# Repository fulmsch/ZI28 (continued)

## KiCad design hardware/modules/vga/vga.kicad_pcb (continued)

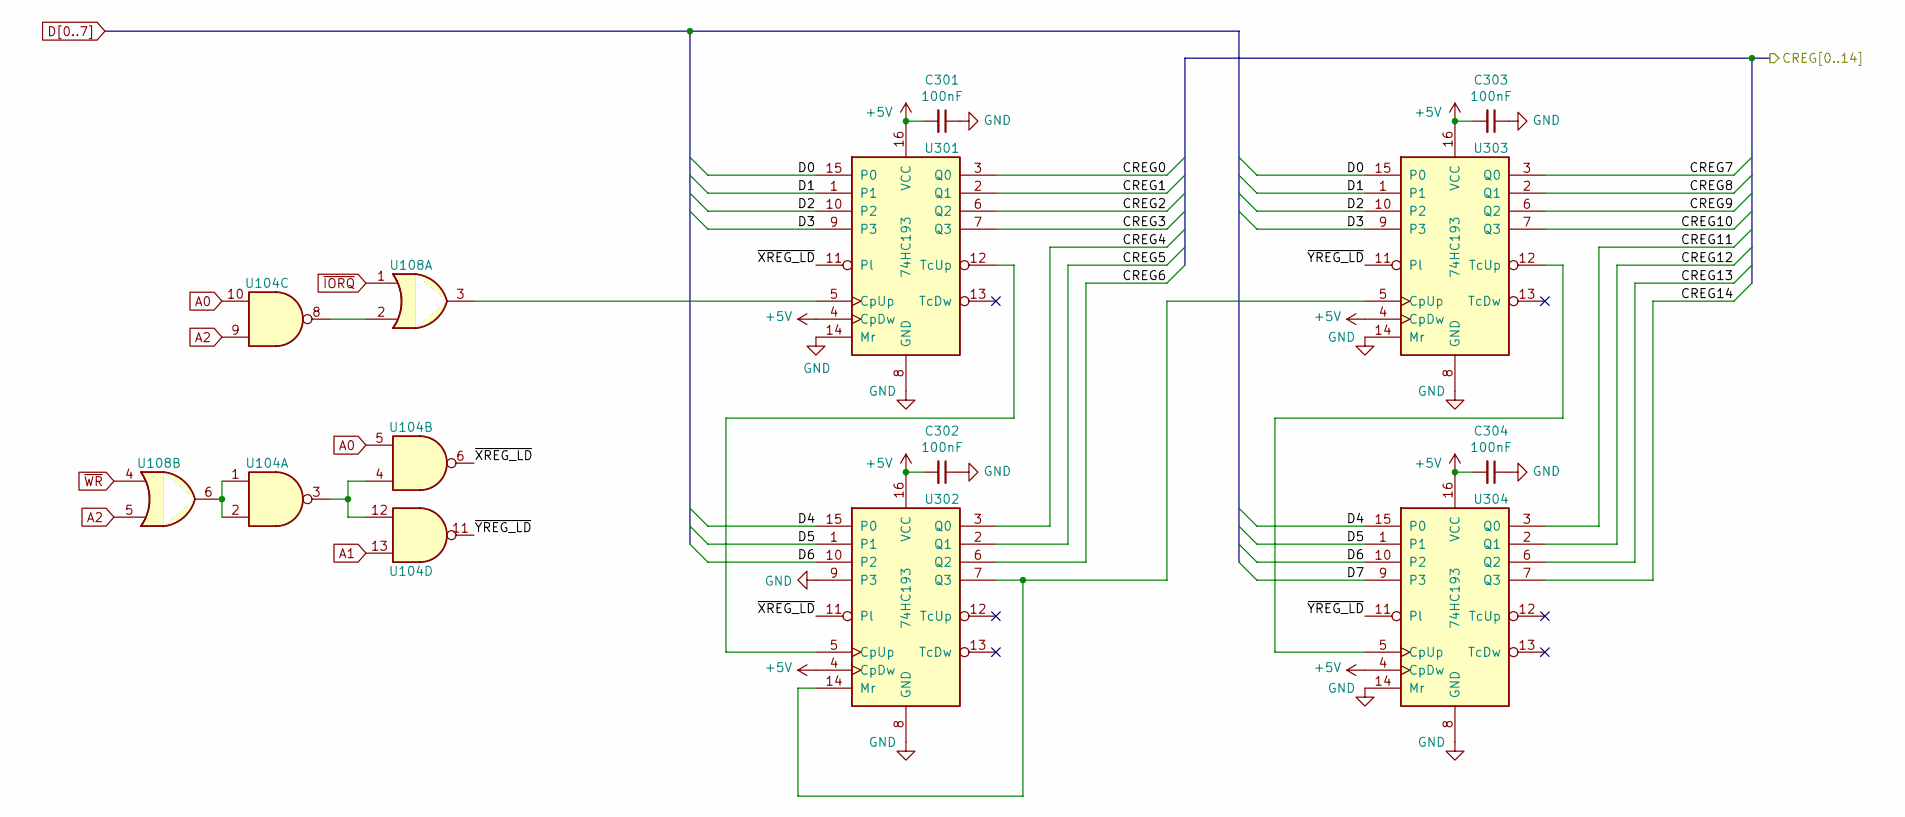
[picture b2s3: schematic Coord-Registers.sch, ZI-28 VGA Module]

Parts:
C301, C302, C303, C304: 100nF; C_Disc_D3.0mm_W1.6mm_P2.50mm
U104: 74HC00; DIP-14_W7.62mm_Socket
U108: 74HC32; DIP-14_W7.62mm_Socket
U301, U302, U303, U304: 74HC193; DIP-16_W7.62mm_Socket

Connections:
+5V: C301.2, C302.2, C303.2, C304.2, U301.4 (CpDw), U301.16 (VCC), U302.4 (CpDw), U302.16 (VCC), U303.4 (CpDw), U303.16 (VCC), U304.4 (CpDw), U304.16 (VCC); also elsewhere on the board
/Coordinate Registers/CREG0: U301.3 (Q0); also elsewhere on the board
/Coordinate Registers/CREG1: U301.2 (Q1); also elsewhere on the board
/Coordinate Registers/CREG2: U301.6 (Q2); also elsewhere on the board
/Coordinate Registers/CREG3: U301.7 (Q3); also elsewhere on the board
/Coordinate Registers/CREG4: U302.3 (Q0); also elsewhere on the board
/Coordinate Registers/CREG5: U302.2 (Q1); also elsewhere on the board
/Coordinate Registers/CREG6: U302.6 (Q2); also elsewhere on the board
/Coordinate Registers/CREG7: U303.3 (Q0); also elsewhere on the board
/Coordinate Registers/CREG8: U303.2 (Q1); also elsewhere on the board
/Coordinate Registers/CREG9: U303.6 (Q2); also elsewhere on the board
/Coordinate Registers/CREG10: U303.7 (Q3); also elsewhere on the board
/Coordinate Registers/CREG11: U304.3 (Q0); also elsewhere on the board
/Coordinate Registers/CREG12: U304.2 (Q1); also elsewhere on the board
/Coordinate Registers/CREG13: U304.6 (Q2); also elsewhere on the board
/Coordinate Registers/CREG14: U304.7 (Q3); also elsewhere on the board
/Coordinate Registers/~XREG_LD: U104.6, U301.11 (Pl), U302.11 (Pl)
/Coordinate Registers/~YREG_LD: U104.11, U303.11 (Pl), U304.11 (Pl)
A0: U104.5, U104.10; also elsewhere on the board
A1: U104.13; also elsewhere on the board
A2: U104.9, U108.5; also elsewhere on the board
D0: U301.15 (P0), U303.15 (P0); also elsewhere on the board
D1: U301.1, U303.1; also elsewhere on the board
D2: U301.10 (P2), U303.10 (P2); also elsewhere on the board
D3: U301.9 (P3), U303.9 (P3); also elsewhere on the board
D4: U302.15 (P0), U304.15 (P0); also elsewhere on the board
D5: U302.1, U304.1; also elsewhere on the board
D6: U302.10 (P2), U304.10 (P2); also elsewhere on the board
D7: U304.9 (P3); also elsewhere on the board
GND: C301.1, C302.1, C303.1, C304.1, U301.8 (GND), U301.14 (Mr), U302.8 (GND), U302.9 (P3), U303.8 (GND), U303.14 (Mr), U304.8 (GND), U304.14 (Mr); also elsewhere on the board
unnamed: U104.1, U104.2, U108.6
unnamed: U104.8, U108.2
unnamed: U104.3, U104.4, U104.12
unnamed: U108.3, U301.5 (CpUp)
unnamed: U301.12 (TcUp), U302.5 (CpUp)
unnamed: U302.7 (Q3), U302.14 (Mr), U303.5 (CpUp)
unnamed: U303.12 (TcUp), U304.5 (CpUp)
~IORQ: U108.1; also elsewhere on the board
~WR: U108.4; also elsewhere on the board

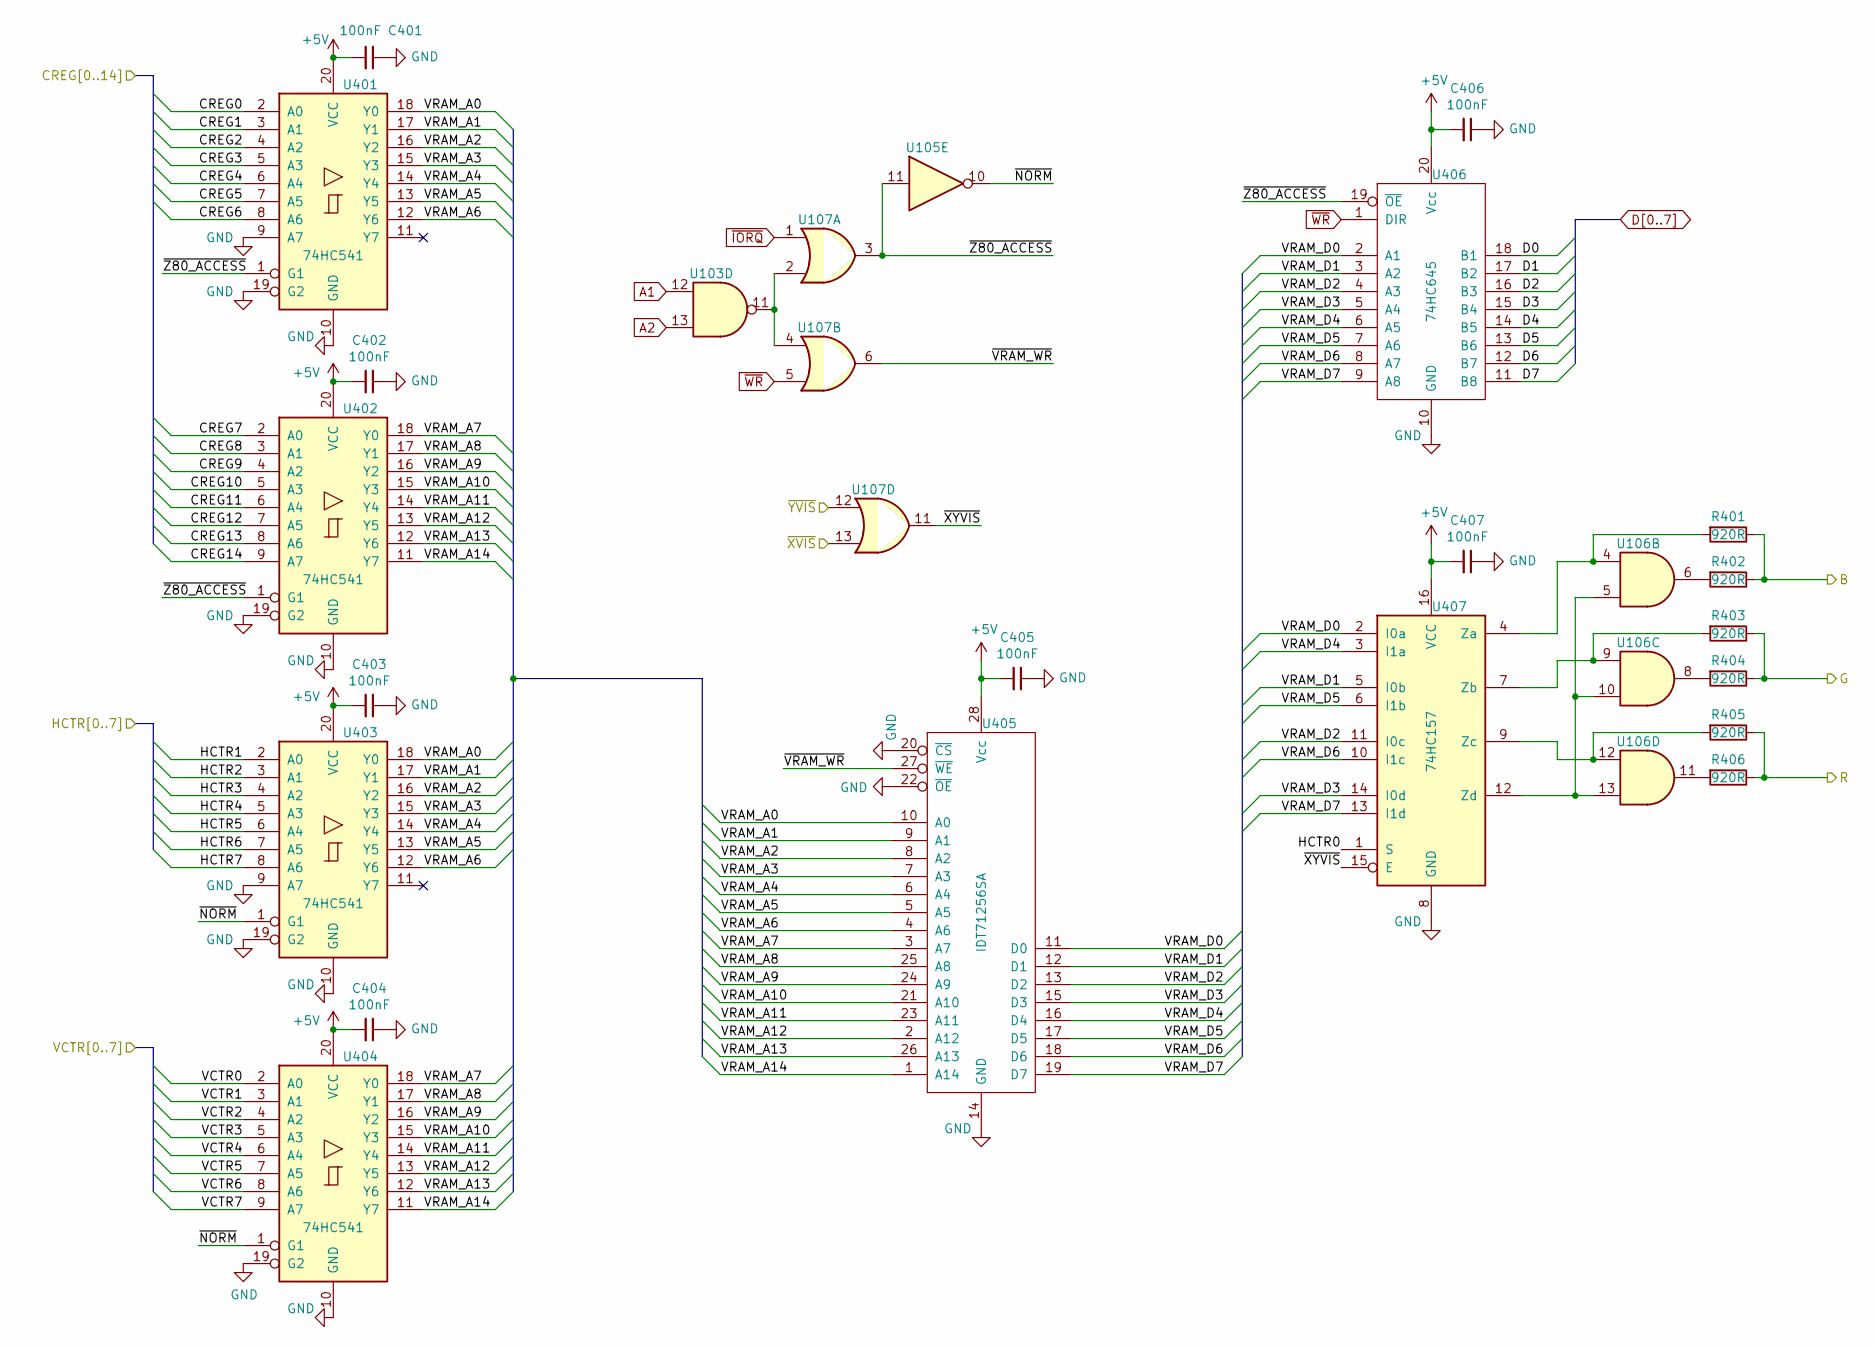
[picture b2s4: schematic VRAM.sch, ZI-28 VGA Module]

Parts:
C401, C402, C403, C404, C405, C406, C407: 100nF; C_Disc_D3.0mm_W1.6mm_P2.50mm
R401, R402, R403, R404, R405, R406: 920R; R_Axial_DIN0207_L6.3mm_D2.5mm_P2.54mm_Vertical
U103: 74HC00; DIP-14_W7.62mm_Socket
U105: 74HC04; DIP-14_W7.62mm_Socket
U106: 74HC08; DIP-14_W7.62mm_Socket
U107: 74HC32; DIP-14_W7.62mm_Socket
U401, U402, U403, U404: 74HC541; DIP-20_W7.62mm_Socket
U405: IDT71256SA; DIP-28_W7.62mm_Socket
U406: 74HC645; DIP-20_W7.62mm_Socket
U407: 74HC157; DIP-16_W7.62mm_Socket

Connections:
+5V: C401.2, C402.2, C403.2, C404.2, C405.2, C406.2, C407.2, U401.20 (VCC), U402.20 (VCC), U403.20 (VCC), U404.20 (VCC), U405.28 (Vcc), U406.20 (Vcc), U407.16 (VCC); also elsewhere on the board
/BLUE: R401.1, R402.1; also elsewhere on the board
/Coordinate Registers/CREG0: U401.2 (A0); also elsewhere on the board
/Coordinate Registers/CREG1: U401.3 (A1); also elsewhere on the board
/Coordinate Registers/CREG2: U401.4 (A2); also elsewhere on the board
/Coordinate Registers/CREG3: U401.5 (A3); also elsewhere on the board
/Coordinate Registers/CREG4: U401.6 (A4); also elsewhere on the board
/Coordinate Registers/CREG5: U401.7 (A5); also elsewhere on the board
/Coordinate Registers/CREG6: U401.8 (A6); also elsewhere on the board
/Coordinate Registers/CREG7: U402.2 (A0); also elsewhere on the board
/Coordinate Registers/CREG8: U402.3 (A1); also elsewhere on the board
/Coordinate Registers/CREG9: U402.4 (A2); also elsewhere on the board
/Coordinate Registers/CREG10: U402.5 (A3); also elsewhere on the board
/Coordinate Registers/CREG11: U402.6 (A4); also elsewhere on the board
/Coordinate Registers/CREG12: U402.7 (A5); also elsewhere on the board
/Coordinate Registers/CREG13: U402.8 (A6); also elsewhere on the board
/Coordinate Registers/CREG14: U402.9 (A7); also elsewhere on the board
/GREEN: R403.1, R404.1; also elsewhere on the board
/Pixel Counters/HCTR0: U407.1 (S); also elsewhere on the board
/Pixel Counters/HCTR1: U403.2 (A0); also elsewhere on the board
/Pixel Counters/HCTR2: U403.3 (A1); also elsewhere on the board
/Pixel Counters/HCTR3: U403.4 (A2); also elsewhere on the board
/Pixel Counters/HCTR4: U403.5 (A3); also elsewhere on the board
/Pixel Counters/HCTR5: U403.6 (A4); also elsewhere on the board
/Pixel Counters/HCTR6: U403.7 (A5); also elsewhere on the board
/Pixel Counters/HCTR7: U403.8 (A6); also elsewhere on the board
/Pixel Counters/VCTR6: U404.8 (A6); also elsewhere on the board
/Pixel Counters/VCTR7: U404.9 (A7); also elsewhere on the board
/RED: R405.1, R406.1; also elsewhere on the board
/VCTR0: U404.2 (A0); also elsewhere on the board
/VCTR1: U404.3 (A1); also elsewhere on the board
/VCTR2: U404.4 (A2); also elsewhere on the board
/VCTR3: U404.5 (A3); also elsewhere on the board
/VCTR4: U404.6 (A4); also elsewhere on the board
/VCTR5: U404.7 (A5); also elsewhere on the board
/VRAM/VRAM_A0: U401.18 (Y0), U403.18 (Y0), U405.10 (A0)
/VRAM/VRAM_A1: U401.17 (Y1), U403.17 (Y1), U405.9 (A1)
/VRAM/VRAM_A2: U401.16 (Y2), U403.16 (Y2), U405.8 (A2)
/VRAM/VRAM_A3: U401.15 (Y3), U403.15 (Y3), U405.7 (A3)
/VRAM/VRAM_A4: U401.14 (Y4), U403.14 (Y4), U405.6 (A4)
/VRAM/VRAM_A5: U401.13 (Y5), U403.13 (Y5), U405.5 (A5)
/VRAM/VRAM_A6: U401.12 (Y6), U403.12 (Y6), U405.4 (A6)
/VRAM/VRAM_A7: U402.18 (Y0), U404.18 (Y0), U405.3 (A7)
/VRAM/VRAM_A8: U402.17 (Y1), U404.17 (Y1), U405.25 (A8)
/VRAM/VRAM_A9: U402.16 (Y2), U404.16 (Y2), U405.24 (A9)
/VRAM/VRAM_A10: U402.15 (Y3), U404.15 (Y3), U405.21 (A10)
/VRAM/VRAM_A11: U402.14 (Y4), U404.14 (Y4), U405.23 (A11)
/VRAM/VRAM_A12: U402.13 (Y5), U404.13 (Y5), U405.2 (A12)
/VRAM/VRAM_A13: U402.12 (Y6), U404.12 (Y6), U405.26 (A13)
/VRAM/VRAM_A14: U402.11 (Y7), U404.11 (Y7), U405.1 (A14)
/VRAM/VRAM_D0: U405.11 (D0), U406.2 (A1), U407.2 (I0a)
/VRAM/VRAM_D1: U405.12 (D1), U406.3 (A2), U407.5 (I0b)
/VRAM/VRAM_D2: U405.13 (D2), U406.4 (A3), U407.11 (I0c)
/VRAM/VRAM_D3: U405.15 (D3), U406.5 (A4), U407.14 (I0d)
/VRAM/VRAM_D4: U405.16 (D4), U406.6 (A5), U407.3 (I1a)
/VRAM/VRAM_D5: U405.17 (D5), U406.7 (A6), U407.6 (I1b)
/VRAM/VRAM_D6: U405.18 (D6), U406.8 (A7), U407.10 (I1c)
/VRAM/VRAM_D7: U405.19 (D7), U406.9 (A8), U407.13 (I1d)
/VRAM/~NORM: U105.10, U403.1 (G1), U404.1 (G1)
/VRAM/~VRAM_WR: U107.6, U405.27 (~WE)
/VRAM/~XYVIS: U107.11, U407.15 (E)
/VRAM/~Z80_ACCESS: U105.11, U107.3, U401.1 (G1), U402.1 (G1), U406.19 (~OE)
/~XVIS: U107.13; also elsewhere on the board
/~YVIS: U107.12; also elsewhere on the board
A1: U103.12; also elsewhere on the board
A2: U103.13; also elsewhere on the board
D0: U406.18 (B1); also elsewhere on the board
D1: U406.17 (B2); also elsewhere on the board
D2: U406.16 (B3); also elsewhere on the board
D3: U406.15 (B4); also elsewhere on the board
D4: U406.14 (B5); also elsewhere on the board
D5: U406.13 (B6); also elsewhere on the board
D6: U406.12 (B7); also elsewhere on the board
D7: U406.11 (B8); also elsewhere on the board
GND: C401.1, C402.1, C403.1, C404.1, C405.1, C406.1, C407.1, U401.9 (A7), U401.10 (GND), U401.19 (G2), U402.10 (GND), U402.19 (G2), U403.9 (A7), U403.10 (GND), U403.19 (G2), U404.10 (GND), U404.19 (G2), U405.14 (GND), U405.20 (~CS), U405.22 (~OE), U406.10 (GND), U407.8 (GND); also elsewhere on the board
unnamed: R401.2, U106.4, U407.4 (Za)
unnamed: R402.2, U106.6
unnamed: R403.2, U106.9, U407.7 (Zb)
unnamed: R404.2, U106.8
unnamed: R405.2, U106.12, U407.9 (Zc)
unnamed: R406.2, U106.11
unnamed: U103.11, U107.2, U107.4
unnamed: U106.5, U106.10, U106.13, U407.12 (Zd)
~IORQ: U107.1; also elsewhere on the board
~WR: U107.5, U406.1 (DIR); also elsewhere on the board

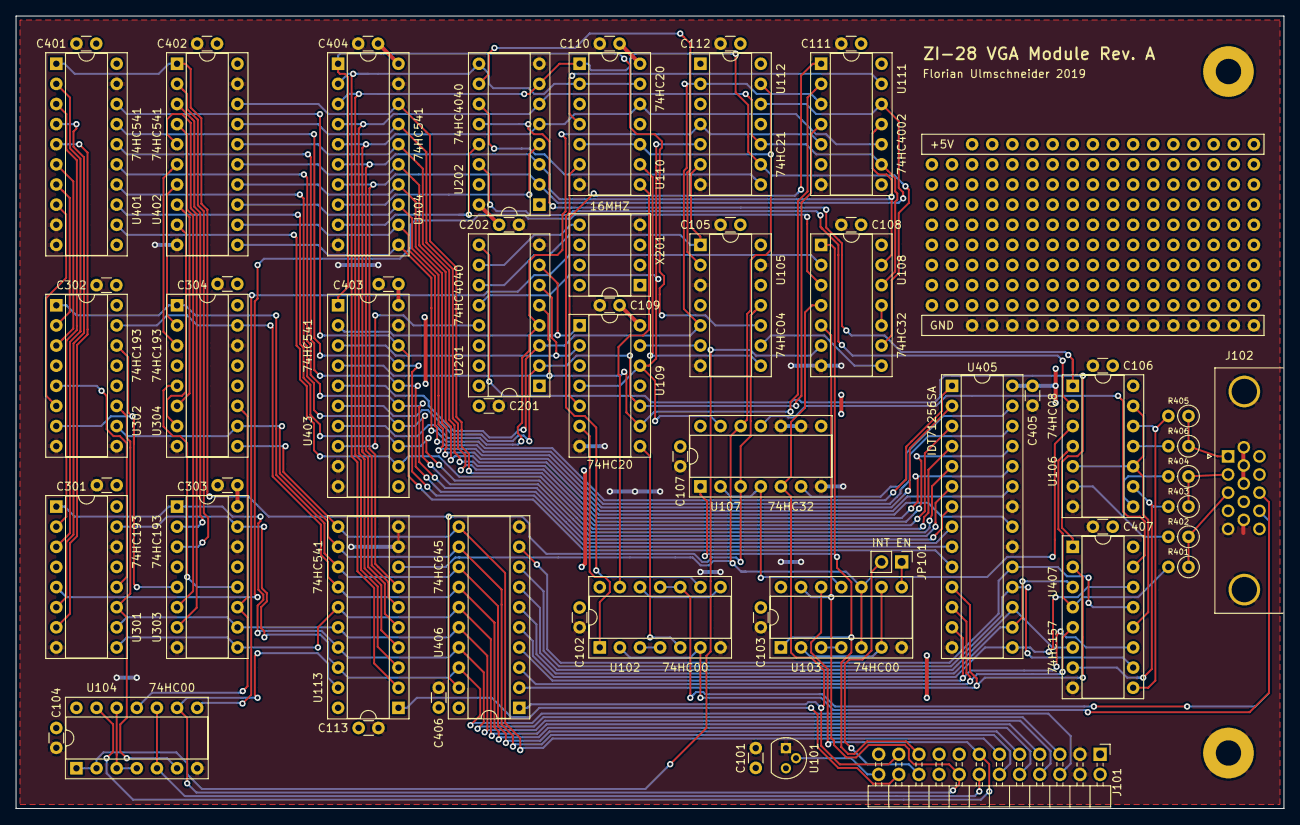
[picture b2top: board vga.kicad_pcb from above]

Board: 2 copper layers, 160.0 x 100.0 mm, 64 parts (0 on the bottom side), 121 nets.

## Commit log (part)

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2016-10-12 Fixed Makefiles
2016-10-12 Added readme for emulator
2016-10-12 Added distinction between invalid MBR and bootloader
2016-10-12 Fixed FAT address calculation
2016-10-13 Added FAT2 calc, changed to sectors instead of addresses
2016-10-13 Added calculation of root dir and data region
2016-10-13 Created adding subroutine
2016-10-16 Added function to search for file
2016-10-16 Added functionality for opening files
2016-10-17 Added basic file reading
2016-10-18 Added path resolving when opening files
2016-10-18 Filenames now get converted to uppercase automatically
2016-10-18 Read automatically gets limited to the file size
2016-10-19 Both stages of the bootloader are functional
2016-10-21 Fixed file size offsets
2016-10-21 Added temporary boot sequence
2016-10-23 Added two games
2016-10-23 Changed prompt
2016-11-20 Migrated away from Atmel Studio
2016-12-03 Expanded .gitignore
2016-12-03 Added file closing
2016-12-06 Added checking if the user specified a full programm path
2016-12-10 Migrated project to naken_asm
2016-12-10 Fixed Makefiles and nullterminators
2016-12-11 Added help command
2016-12-14 Added tool to build relocatable asm files
2016-12-14 Completed build tool
2016-12-16 Added more bcos calls
2016-12-29 Started vfs
2016-12-29 Switched emulator from c to c++
2016-12-29 Added framework for modules
2016-12-30 Fixed command detection
2016-12-30 Implemented multiple block read
2016-12-30 Fixed wrong SDC block size
2017-01-03 Changed to c
2017-01-03 The pty-pair gets created in the main program
2017-01-03 Moved emulator functions to separate file
2017-01-03 Added GTK UI
2017-01-05 Added basic breakpoint functionality
2017-01-12 Added background mode without gui
2017-01-19 Started restructuring filesystem
2017-01-21 Limited the frequency in a very hacky way
2017-01-26 Merged OS and BIOS, OS is now in ROM
2017-01-27 Moved all OS variables to RAM
2017-01-28 Added/changed string routines
2017-01-29 Began work on device filesystem
2017-01-30 Restructured internal commands
2017-01-31 Started mounting functionality
2017-01-31 Added functionality to open and read from devices
2017-02-02 Added file write, changed printStr to write to file
2017-02-09 Small fixes
2017-02-14 Added specification for k_seek
2017-02-17 SD-Card driver outline
2017-02-19 Added 32-bit math routines
2017-02-20 Added 32-bit subtraction
2017-02-28 Added k_seek
2017-03-21 First implementation of documentation utility
2017-03-21 Redundancy check in listing of files
2017-03-21 Updated templates
2017-03-21 Restructured directory
2017-03-21 Updated documentation
2017-03-21 Short description is the first paragraph
2017-03-21 Fixed short description
2017-03-21 Added conditions to templates
2017-03-26 Restructuring
2017-03-28 SDC-Driver basic structure
2017-03-28 Updated Makefile
2017-03-28 Menu option for ROM write protection
2017-03-28 UI tweak
2017-04-01 Block access layer
2017-04-01 Removed file type distinction
2017-04-01 Fixed and expanded 32-bit shifts
2017-04-01 Added main flag display
2017-04-02 Added support for single block read
2017-04-02 Testing & fixes
2017-04-04 Sector offset in SD-driver
2017-04-04 Added routine to populate devfs
2017-04-04 RAM is cleared at coldstart
2017-04-10 New SD init, bugfixes
2017-04-10 SD debugging info
2017-04-11 UI changes
2017-04-12 FAT init rework
2017-04-15 Reformating
2017-04-15 Count gets added to offset when reading from file
2017-04-16 New FAT16 init routine
2017-04-16 Added 16-bit seek
2017-04-20 Basic implementation of a memory editor using gtkhex
2017-04-21 FAT offsets are stored in bytes instead of sectors
2017-04-22 Routine for following a cluster chain
2017-04-24 Added dec32, fixed inc32
2017-05-09 FAT16 open and read
2017-05-09 Fix for maximum filename length
2017-05-10 Dir entry address gets stored on fat_open
2017-05-11 File modes
2017-05-11 Fixed symolic offsets
2017-05-12 fstat and readdir
2017-05-14 Changed path syntax
2017-05-14 Updated mount command
2017-05-14 Fixed RAM clearing
2017-06-16 Automatically mount the main drive
2017-06-27 Separated file descriptor and file table
2017-06-27 Standard streams
2017-07-19 Added system call interface
2017-07-20 Basic implementation of exec
2017-07-21 Makefile rule to run the emulator
2017-07-24 Ft240 now correctly returns the last char if no new one is available
2017-07-25 C library functional
2017-07-26 Combined C and asm includes
2017-07-28 Started adding system calls to C lib
2017-08-02 Fixed std streams
2017-08-03 Made printf work
2017-08-05 Fixed stat
2017-08-06 Terminate argv
2017-08-06 Permanently set RAM-model in crt
2017-08-06 Fixed filetype test macros
2017-08-09 Add a basic implementation of argument passing
2017-08-10 Add realpath routine
2017-08-11 Expand realpath to fully convert all paths
2017-08-11 Change the way bitmaps work
2017-08-11 Remove unneeded field from fileTable
2017-08-11 Fix file type and mode
2017-08-11 Fix relative path handling
2017-08-11 Remove unneeded code
2017-08-11 Fix crash with drive without trailing slash
2017-08-12 Print working directory in prompt
2017-08-12 Add searching the execution path
2017-08-12 Clean up
2017-08-13 Add readdir and fstat to devfs
2017-08-13 Fix buffer overflow
2017-08-14 Fix terminal carriage return
2017-08-14 Move file extension handling to exec
2017-08-20 Add clear screen command
2017-08-27 Fix starting address of RAM
2017-08-30 Add SD write support
2017-08-30 Add sd_writeBlock and test command
2017-08-31 Fix makefile of romutil
2017-08-31 Add block write routine
2017-08-31 Reduce code duplication in block driver
2017-09-02 Add SD busy check before sending command
2017-09-02 Implement basic fat_write based on fat_read
2017-09-03 Try to add gtkhex to main window
2017-10-02 Fix console (terminal mode, potential buffer overflow)
2017-10-03 Add automatic cleanup on termination
2017-10-03 Add long options
2017-10-15 Expand ROM size to 16kB
2017-10-27 Add routines for allocating new clusters
2017-10-27 Fix register in fat_nextCluster
2017-10-27 Fix path resolution
2017-10-27 Fix syscall stack error
2017-10-27 Restructure OS source tree
2017-10-27 Add file expansion to fat_write
2017-10-27 Include '.' and '..' in readdir
2017-10-27 Add .EX8 to gitignore
2017-10-27 Add hardcoded offset for different SD image
2017-10-27 Fix line termination
2017-10-27 Improve terminal character handling
2017-10-27 Add writing to empty files, doesn't work yet
2017-10-31 Fix writing to empty files
2017-11-07 Fix fat_write incorrectly increasing file size of directories
2017-11-07 Add build time to VER command
2017-11-08 Add banking support to emulator
2017-11-16 Add romutil to bootloader.
2017-12-01 Add unlink
2017-12-01 Change memory layout
2017-12-01 Fix fstat for FAT root directory
2017-12-01 Restructure C library
2017-12-02 Restructure repository
2017-12-04 Integrate libz80.
2017-12-06 Rename emulator
2017-12-06 Fix and expand makefiles
2017-12-07 Rename make config file.
2017-12-07 Emulator automatically starts in text mode if there's no display server.
2017-12-07 Add tools for disk image management.
2017-12-17 Restructure header files.
2017-12-18 Add more programs, expand user build system
2017-12-18 Add command line parameter for sd image to emulator.
2017-12-19 Add guessing game to build system.
2017-12-25 Change filesystem structure to UNIX-like tree.
2017-12-25 Update run targets in Makefiles.
2017-12-25 Remove chmain builtin.
2017-12-26 Fix libz80 include.
2017-12-26 Set gtk version to 3.16.
2017-12-26 Set ZCCCFG before invoking zcc.
2017-12-27 Add strerror.
2017-12-27 Rename rst labels.
2017-12-27 Optimise board generation.
2017-12-28 Add heap initialisation to crt.
2017-12-30 Start transition from naken_asm to z88dk-z80asm.
2018-01-01 Port bootloader to z80asm.
2018-01-02 Fix header name.
2018-01-03 Add lseek to clib.
2018-01-03 Remove relocation tool.
2018-01-03 Implement basic banking.
2018-01-04 Move most variables to the correct location in ram.
2018-01-04 Fix file test.
2018-01-04 Update readme.
2018-01-05 Fix putc/getc.
2018-01-06 Revert memory layout.
2018-01-11 Update programs to new ram layout.
2018-01-11 Add banking support to bootloader romutil.
2018-01-11 Outline banking system calls.
2018-02-15 Add echo executable.
2018-02-15 Add prototype of execv.
2018-05-22 Add bank request.
2018-05-22 Remove breq and bfree.
2018-05-27 Fix syscall table.
2018-05-27 Change user ram start to 0x8100.
2018-05-27 Redesign execv.
2018-07-05 Simplify bank system.
2018-07-05 Start fork/exec calls and shell.
2018-07-05 Fix tools and makefiles.
2018-07-10 Move shell to own package.
2018-07-11 Add chdir and getcwd system calls.
2018-07-11 Add first builtins to shell.
2018-07-12 Add path and extension checking to shell.
2018-07-12 Remove old kernel shell.
2018-09-11 Fix C lseek wrapper.
2018-09-27 Fix lseek overflow detection.
2018-10-12 Add snake game.
2018-11-13 Add tetris.
2018-11-30 Expand snake game.
2018-11-30 Fix condition reference.
2018-11-30 Add conditional breakpoint handling.
2018-11-30 Add functions for adding trace- and watchpoints.
2018-11-30 Add watchpoint handling.
2018-12-01 Add printInstruction.
2019-01-17 Update Makefile.
2019-01-17 Execute functions even without parentheses.
2019-01-17 Add interface for loadable modules.
2019-01-21 Small changes.
2019-02-07 Add 'next' and 'step'.
2019-02-08 Removed distinction between commands and functions.
2019-03-01 Unsuccessful rewrite of fat read.
2019-03-01 Add errno to clib read.
2019-03-01 Sudoku stuff, incl. debugging.
2019-06-14 Add PS/2 input to keyboard controller.
2019-06-14 Add VGA module PCB.
2019-06-15 Move iomap.h to global include directory.
2019-06-16 Rename & restructure bootloader.
2019-06-16 Add BASIC to bank 0.
2019-06-16 Remove 'run' option from OS makefile.
2019-06-16 Add font table and primitive text rendering routine.
2019-06-16 Add BASIC program.
2019-06-16 Fix vga module naming.
2019-06-16 Fix buffer overflow in kernel shell.
2019-06-16 Shell: Add basic quoting.
2019-06-17 Kernel: Init function for device drivers.
2019-06-17 Kernel: add simple memory allocation.
2019-07-11 Emulator: Randomize VRAM on start.
2019-07-11 OS: Add decimal printing routines.
2019-07-11 OS: Start work on VGA text driver.
2019-07-11 Add programs to test video card.
2019-07-11 New OS based on CamelForth.
2019-09-26 Add forgotten list file for bank0.
2019-10-08 Add config file option to emulator.
2019-10-08 Add block words.
2019-11-23 Temporary fix to prevent rom writing.
2019-11-27 Start moving the OS source to org files.
2019-11-28 Add emulator modules to Makefile.
2019-11-28 OS: Move all code to org files
    However, most files still need a lot of documentation and organisation.
2019-12-02 Emulator: Make creating breakpoints easier
    Breakpoints can now be created without using a pointer (e.g.
    'breakpoint(0x1234)' instead of 'breakpoint(ptr(0x1234))').
2019-12-02 OS: Minor changes
2019-12-02 OS: VT100 emulator for video card
    The VT100 driver can now display monochrome text from a buffer. Writing
    to the buffer works as well, but only to one position.
2019-12-03 OS: Implement backspace and newline in VT100 driver
    Text can now be displayed on the screen, but it is painfully slow as the
    entire screen is redrawn on each write.
2019-12-04 OS: Change font size from 6x8 to 8x8
    This makes it easier to calculate offsets, fills up the entire screen
    and should enable some nice character graphics. On the other hand there
    can now only be 32 characters per line instead of 42.
    Note: Only the code has been changed, the font itself still needs to be adjusted.
2019-12-04 OS: Make text rendering faster by only updating changed characters
    Very hacky implementation, just to see the speed difference. Single
    characters are acceptably fast now, but updating the entire screen when
    scrolling is still very slow.
2019-12-05 OS: Add missing 'ret' in sd_getResponse.
    This was not an issue in the emulator, since the simulated SD card never
    times out. It also seems like it wasn't an issue before restructuring
    the OS as there would have probably been another routine behind it.
2019-12-12 Design new VGA module
    Based on an ICE40 FPGA
2019-12-12 Use existing button
